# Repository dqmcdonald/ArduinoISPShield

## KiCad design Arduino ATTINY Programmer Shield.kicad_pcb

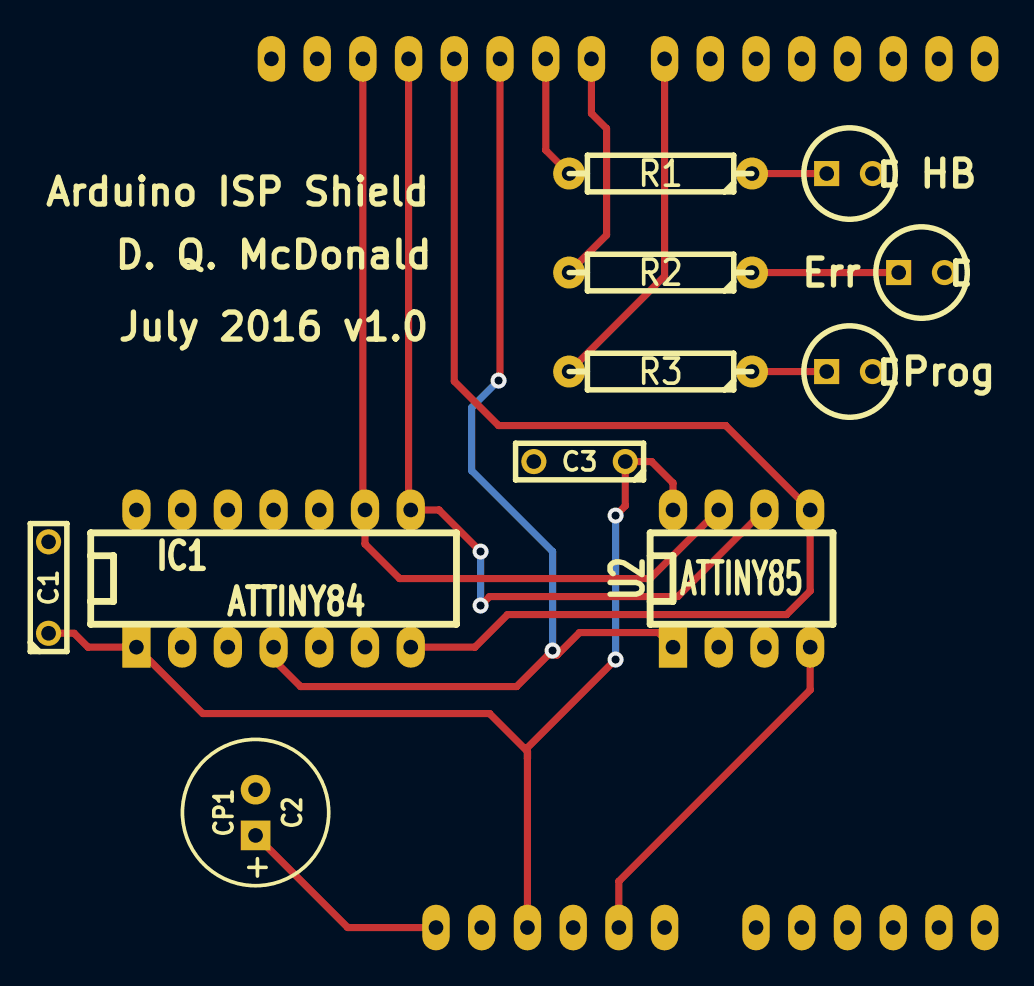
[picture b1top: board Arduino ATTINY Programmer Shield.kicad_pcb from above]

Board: 2 copper layers, 12 parts (0 on the bottom side), 13 nets.

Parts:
C1: 100nf; C2
C2: CP1; C1V8
C3: 100nF; C2
D3: LED; LEDV
Error: LED; LEDV
HeartBeat: LED; LEDV
IC1: ATTINY84; DIP-14__300_ELL
R1: 200R; R4-LARGE_PADS
R2, R3: 220R; R4-LARGE_PADS
SHIELD1: ARDUINO_SHIELD; ARDUINO_SHIELD_2
U2: ATTINY85; DIP-8__300_ELL

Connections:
5V: C1.1, C3.1, IC1.1, SHIELD1.5V, U2.8
GND: C1.2, C2.2, C3.2, D3.2, Error.2, HeartBeat.2, IC1.14, SHIELD1.GND2, U2.4
unnamed: HeartBeat.1, R1.1
unnamed: Error.1, R2.1
unnamed: D3.1, R3.1
Pin7: R3.2, SHIELD1.7
Pin8: R2.2, SHIELD1.8
Pin9: R1.2, SHIELD1.9
Pin10: IC1.4, SHIELD1.10, U2.1
Pin11: IC1.7, SHIELD1.11, U2.5
Pin12: IC1.8, SHIELD1.12, U2.6
Pin13: IC1.9, SHIELD1.13, U2.7
Reset: C2.1, SHIELD1.RST

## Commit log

2016-07-04 Initial version of Arduino ISP shield
    Schematic complete
    Attiny85 and Attiny84
2016-07-05 Added PCB
2016-07-06 Version Sent to OSH Park
